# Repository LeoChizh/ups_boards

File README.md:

# UPS Current-Limited Load Switch

A current-limited, inrush-safe low-side load switch for a battery-backed UPS, built entirely from an NE555 timer and a dual op-amp — no dedicated hot-swap/current-limiter IC.

## What it does

- Switches the return path to a load (in this build: a Raspberry Pi + WiFi router) through an N-channel MOSFET (`Q1`, IRFZ44N).
- A current-sense amplifier (`U1A`) feeding a PWM comparator (`U1B`, both halves of one LM358) fold back the MOSFET's duty cycle as current rises, instead of a hard on/off cutoff or a linear-mode limiter (which would dissipate far more heat at these currents).
- The PWM ramp comes from an NE555 astable (`U2`), tapped directly off the timing capacitor node rather than `OUT`.
- A zener on the 555's `CONT` pin (`D1`, `R1`) pins the ramp's amplitude to a fixed voltage, so the current limit doesn't drift with input voltage (verified across 12–13.8V).
- With `R6` = 10Ω, `R7` = 1k (current-sense gain 101×) and `RSense1` = 0.01Ω: foldback begins around 4A, full cutoff around 8A — independent of supply voltage.
- The switched node also carries a 3×47000µF capacitor bank, so the same foldback loop doubles as inrush-current limiting when charging that bank from empty.

## Files

- `pcb2/pcb1.kicad_sch`, `pcb2/pcb1.kicad_pcb` — the design (KiCad 10)
- `pcb2/myLibrary.pretty/` — custom footprint for the current-sense shunt resistor
- `pcb2/kicad_export_commands.sh` — regenerates the ERC/DRC reports, netlist, and laser-burn artwork (copper layer, mirrored/negative variants, and a silkscreen+values placement guide) from the KiCad source

## Fabrication

Single-sided board. Components are inserted from one face; the copper (opposite face) has its solder mask removed with a laser engraver, then the main power-carrying traces are reinforced with solder for the ~8A current path. See `pcb2/pcb1_Fcu_mirrored.svg` / `pcb2/pcb1_Fcu_mirrored_negative.svg` for the burn artwork and `pcb2/pcb1_Silkscreen_Values.svg` for the component placement guide.

## Status

Built and running — powers a Raspberry Pi 4 and WiFi router off a 12V battery bank, verified across repeated input power cycling with no interruption to the load.

## System schematic

This load switch is one module in the larger UPS. The full system schematic shows how it connects to the rest: mains input through breakers into the AC/DC supply and battery charger, a DPDT relay (`K1`) for mains/battery switchover, over-discharge protection on the battery, and this load switch driving the output USB-C chargers.

`ups_schema/` holds this top-level schematic (KiCad 10, schematic-only — no PCB layout, since it's a system diagram rather than a board to fabricate).

## Build photos

| Enclosure, closed | Enclosure, open |
| --- | --- |
|  |  |

This board is mounted on the enclosure door alongside DIN-rail breakers, an AC-DC power supply (230VAC→12VDC), a battery charger, a main relay (230VAC-coil controlled), and an over-discharge protection board. The front panel carries a voltmeter and two 12V-powered USB-C charging ports.

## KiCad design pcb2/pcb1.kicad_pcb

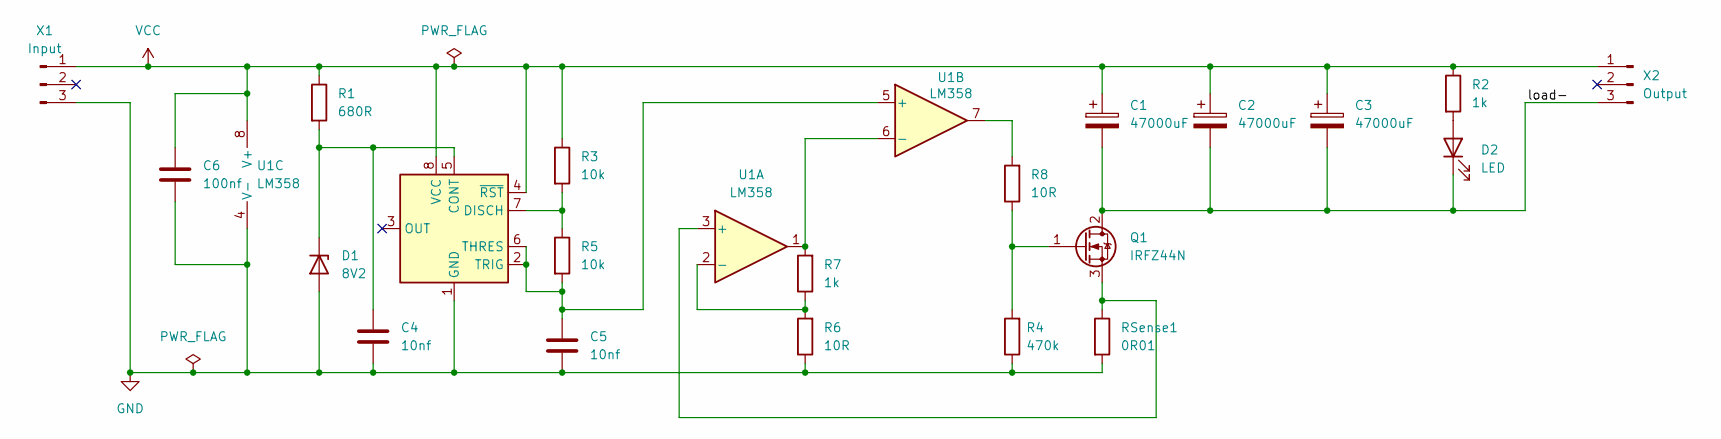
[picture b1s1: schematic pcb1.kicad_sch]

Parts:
C1, C2, C3: 47000uF; CP_Radial_D35.0mm_P10.00mm_SnapIn
C4: 10nf; C_Rect_L7.2mm_W3.5mm_P5.00mm_FKS2_FKP2_MKS2_MKP2
C5: 10nf; C_Rect_L7.0mm_W3.5mm_P5.00mm
C6: 100nf; C_Rect_L9.0mm_W3.3mm_P7.50mm_MKT
D1: 8V2; D_DO-35_SOD27_P7.62mm_Horizontal
D2: LED; LED_D3.0mm_Clear
Q1: IRFZ44N; TO-220-3_Vertical
R1: 680R; R_Axial_DIN0207_L6.3mm_D2.5mm_P10.16mm_Horizontal
R2, R7: 1k; R_Axial_DIN0207_L6.3mm_D2.5mm_P10.16mm_Horizontal
R3, R5: 10k; R_Axial_DIN0207_L6.3mm_D2.5mm_P10.16mm_Horizontal
R4: 470k; R_Axial_DIN0207_L6.3mm_D2.5mm_P10.16mm_Horizontal
R6, R8: 10R; R_Axial_DIN0207_L6.3mm_D2.5mm_P10.16mm_Horizontal
RSense1: 0R01; R_Shunt_d1.2mm_L10mm
U1: LM358; DIP-8_W7.62mm
U2: NE555P; DIP-8_W7.62mm
X1: Input; PhoenixContact_MSTBA_2,5_3-G-5,08_1x03_P5.08mm_Horizontal
X2: Output; PhoenixContact_MSTBA_2,5_3-G-5,08_1x03_P5.08mm_Horizontal

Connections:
/load-: C1.2, C2.2, C3.2, D2.1 (K), Q1.2 (D), X2.3
GND: C4.2, C5.2, C6.2, D1.2 (A), R4.1, R6.1, RSense1.2, U1.4 (V-), U2.1 (GND), X1.3
unnamed: C4.1, D1.1 (K), R1.2, U2.5 (CONT)
unnamed: D2.2 (A), R2.2
unnamed: Q1.1 (G), R4.2, R8.1
unnamed: Q1.3 (S), RSense1.1, U1.3 (+)
unnamed: R8.2, U1.7
unnamed: R6.2, R7.1, U1.2 (-)
unnamed: C5.1, R5.2, U1.5 (+), U2.2 (TRIG), U2.6 (THRES)
unnamed: R7.2, U1.1, U1.6 (-)
unnamed: R3.2, R5.1, U2.7 (DISCH)
VCC: C1.1, C2.1, C3.1, C6.1, R1.1, R2.1, R3.1, U1.8 (V+), U2.4 (~RST), U2.8 (VCC), X1.1, X2.1

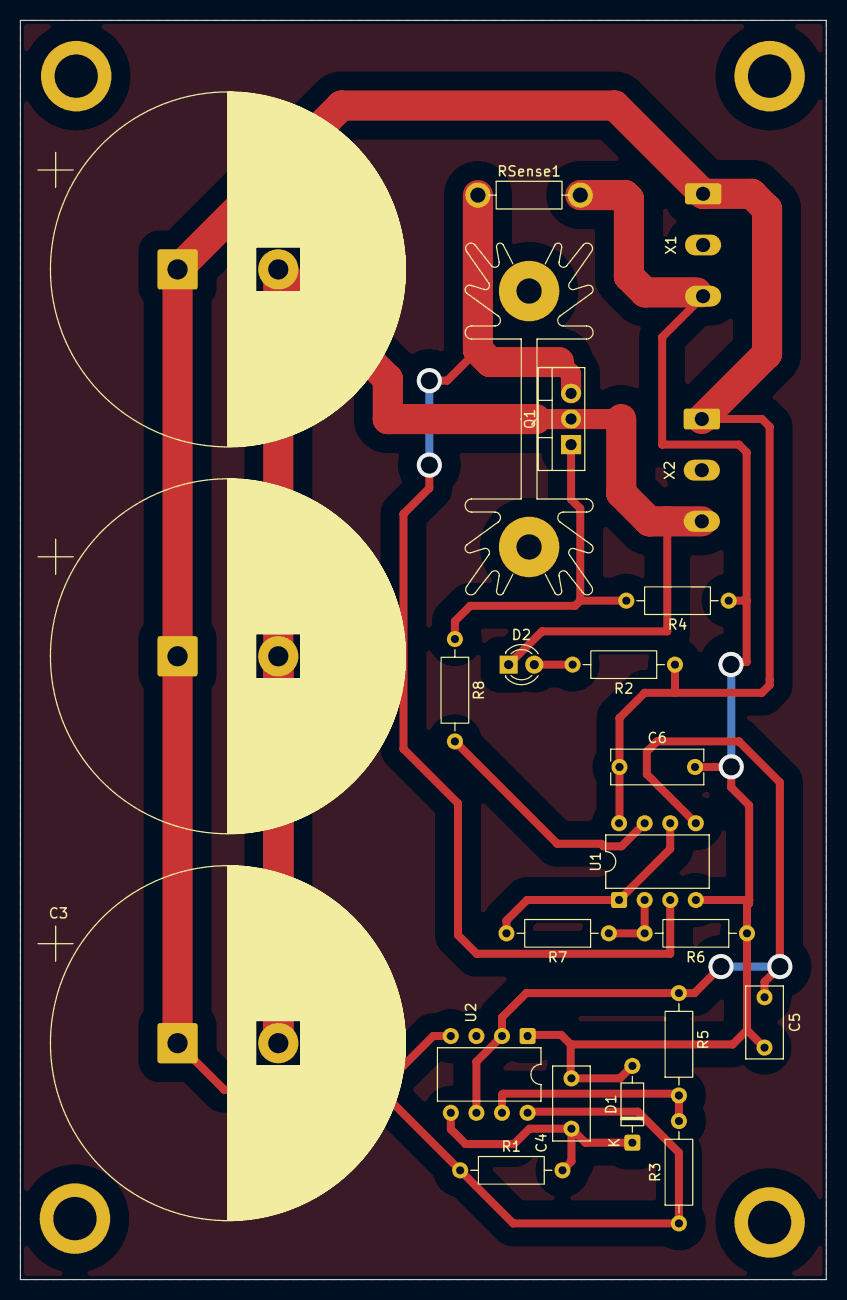
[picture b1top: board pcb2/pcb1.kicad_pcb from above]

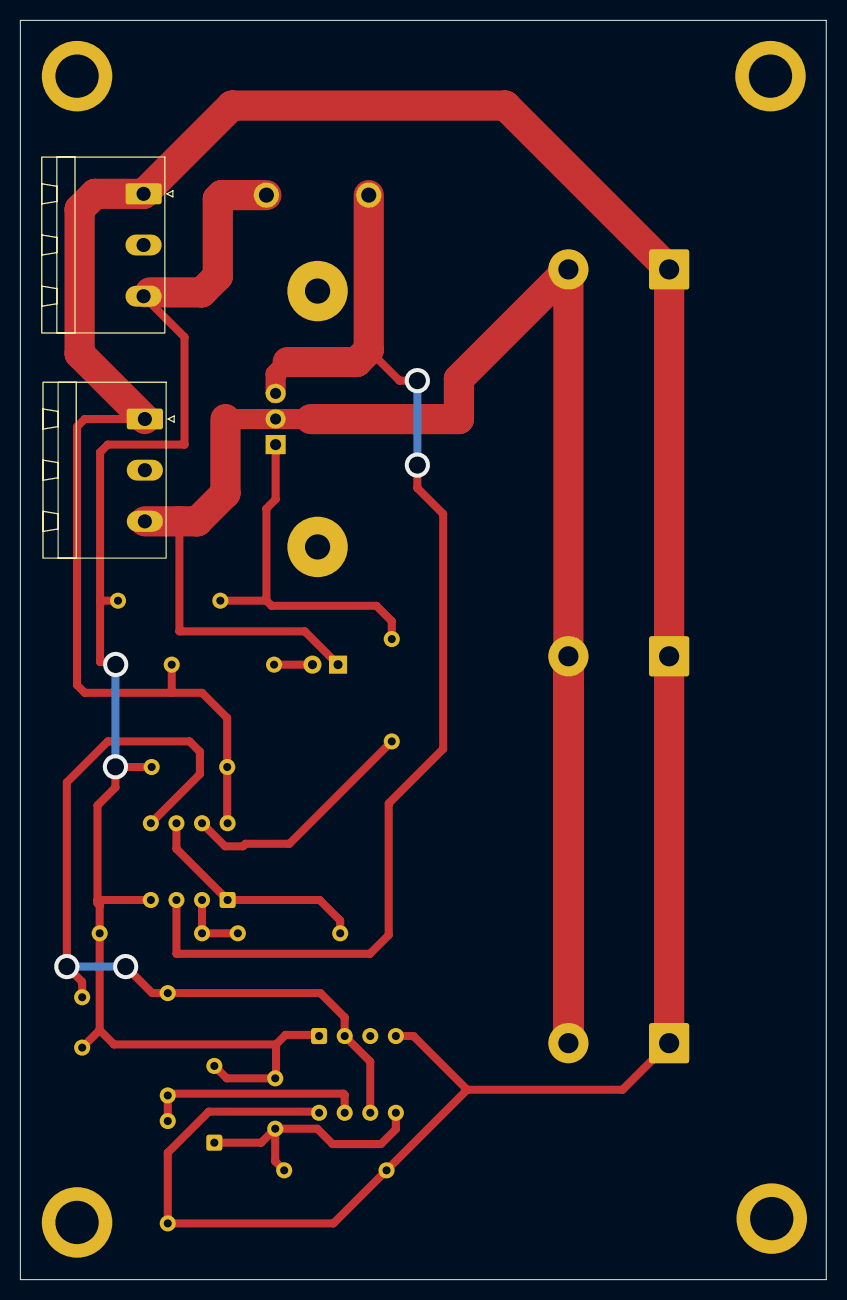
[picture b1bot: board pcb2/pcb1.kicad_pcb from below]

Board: 2 copper layers, 80.0 x 125.0 mm, 26 parts (2 on the bottom side), 12 nets.

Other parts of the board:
mount: MountingHole_4.3mm_M4_ISO14580_Pad
mount#2, mount#3, mount#4: MountingHole_4.3mm_M4_ISO14580_Pad

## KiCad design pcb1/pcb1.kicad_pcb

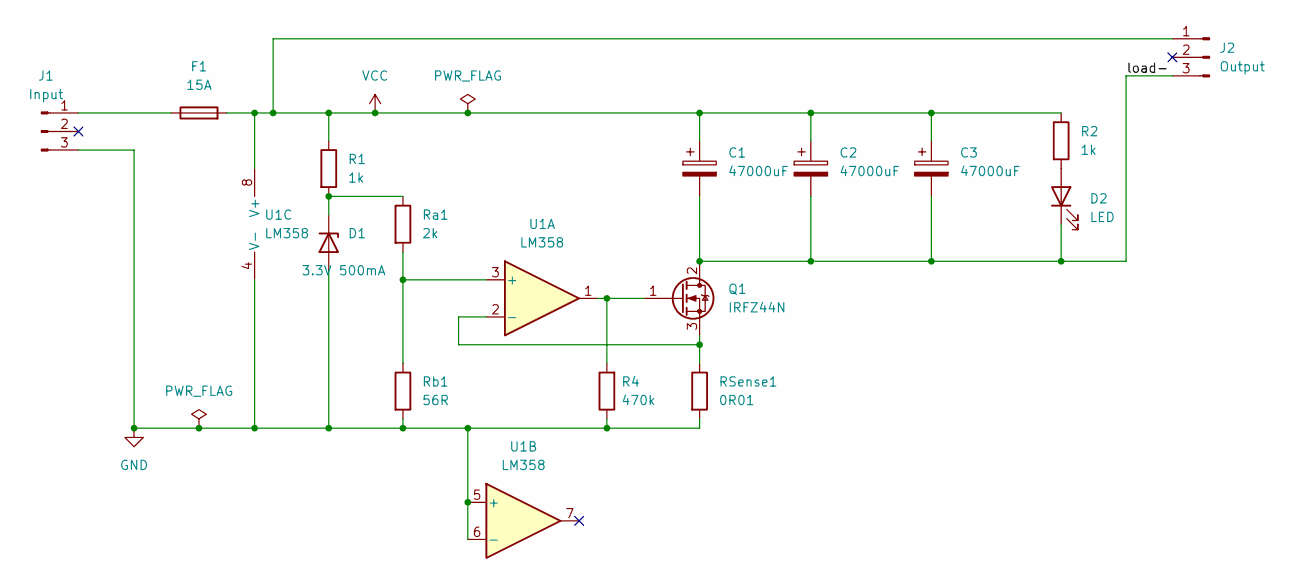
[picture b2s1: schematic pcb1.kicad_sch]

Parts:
C1, C2, C3: 47000uF; CP_Radial_D35.0mm_P10.00mm_SnapIn
D1: 3.3V 500mA; D_DO-35_SOD27_P7.62mm_Horizontal
D2: LED; LED_D3.0mm_Clear
F1: 15A; Fuseholder_Clip-5x20mm_Eaton_1A5601-01_Inline_P20.80x6.76mm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
J1: Input; PhoenixContact_MSTBA_2,5_3-G-5,08_1x03_P5.08mm_Horizontal
J2: Output; PhoenixContact_MSTBA_2,5_3-G-5,08_1x03_P5.08mm_Horizontal
Q1: IRFZ44N; TO-220-3_Vertical
R1, R2: 1k; R_Axial_DIN0207_L6.3mm_D2.5mm_P10.16mm_Horizontal
R4: 470k; R_Axial_DIN0207_L6.3mm_D2.5mm_P10.16mm_Horizontal
RSense1: 0R01; R_Shunt_d1.2mm_L10mm
Ra1: 2k; R_Axial_DIN0207_L6.3mm_D2.5mm_P10.16mm_Horizontal
Rb1: 56R; R_Axial_DIN0207_L6.3mm_D2.5mm_P10.16mm_Horizontal
U1: LM358; DIP-8_W7.62mm

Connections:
/load-: C1.2, C2.2, C3.2, D2.1 (K), J2.3, Q1.2 (D)
GND: D1.2 (A), J1.3, R4.1, RSense1.2, Rb1.2, U1.4 (V-), U1.5 (+), U1.6 (-)
unnamed: D1.1 (K), R1.2, Ra1.1
unnamed: D2.2 (A), R2.2
unnamed: F1.1, J1.1
unnamed: Q1.1 (G), R4.2, U1.1
unnamed: Q1.3 (S), RSense1.1, U1.2 (-)
unnamed: Ra1.2, Rb1.1, U1.3 (+)
VCC: C1.1, C2.1, C3.1, F1.2, J2.1, R1.1, R2.1, U1.8 (V+)

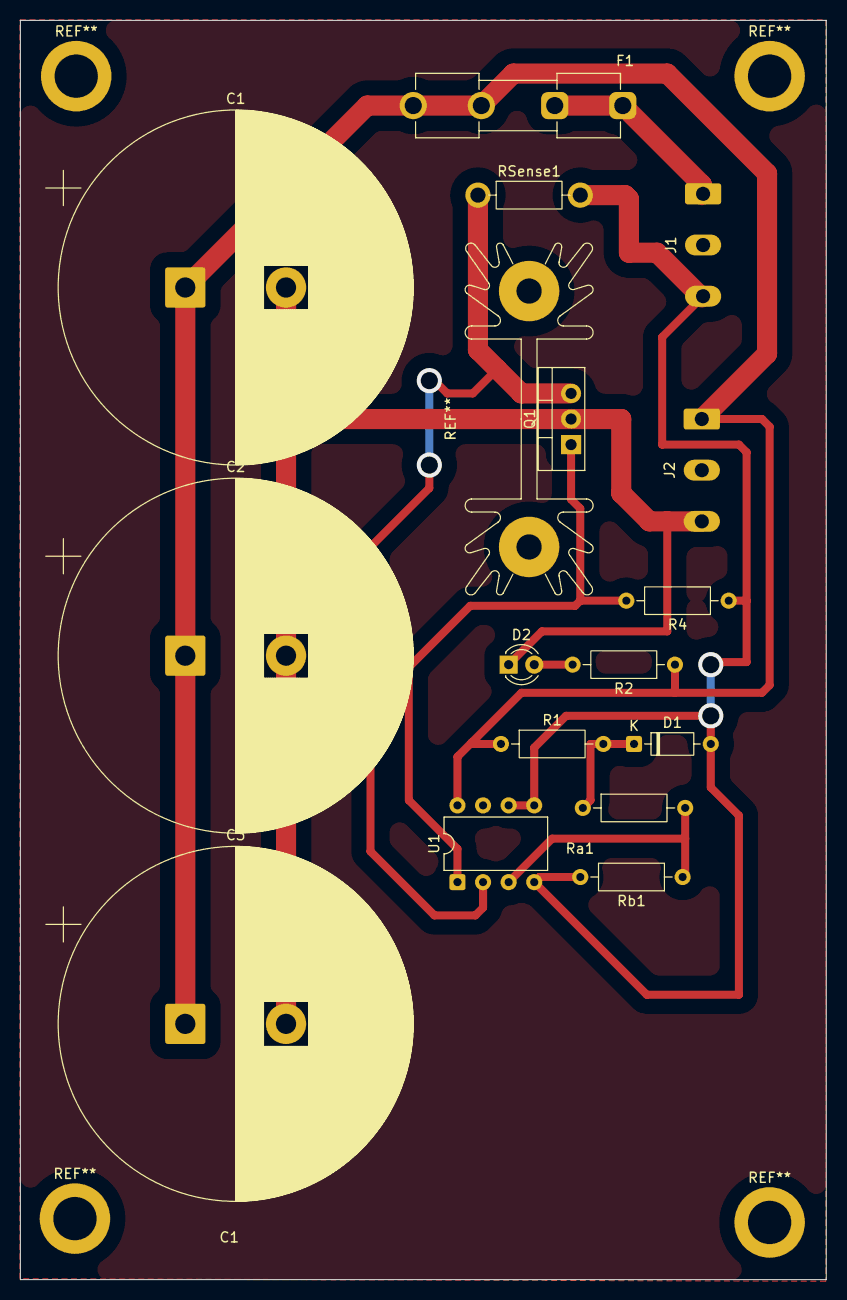
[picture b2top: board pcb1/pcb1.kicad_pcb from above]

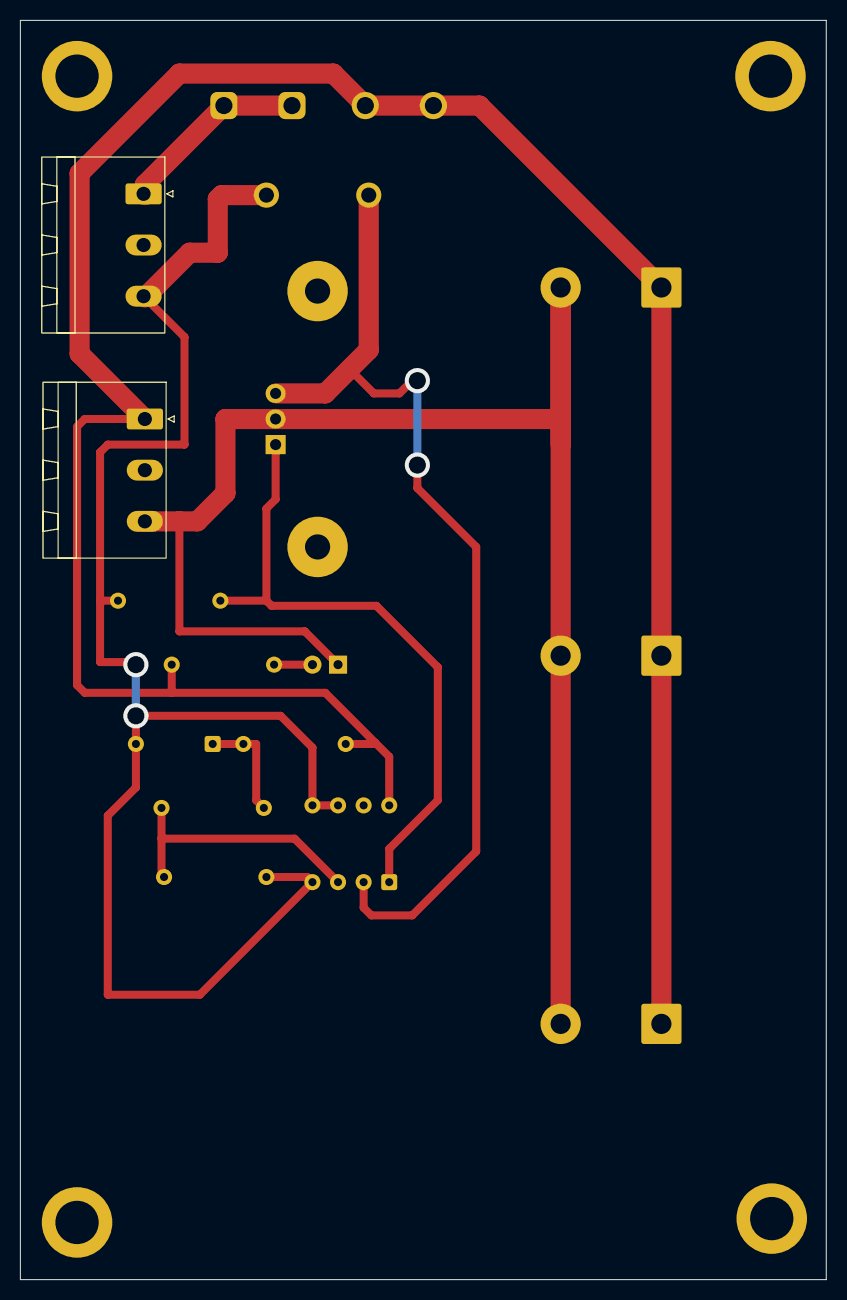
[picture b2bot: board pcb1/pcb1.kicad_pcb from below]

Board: 2 copper layers, 80.0 x 125.0 mm, 16 parts (2 on the bottom side), 9 nets.
